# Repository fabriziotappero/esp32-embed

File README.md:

# ESP32 Embed
This repository contains a lot of C++ projects that can help you out when doing embedded programming with the Espressif ESP32, especially the new ESP32-S2.

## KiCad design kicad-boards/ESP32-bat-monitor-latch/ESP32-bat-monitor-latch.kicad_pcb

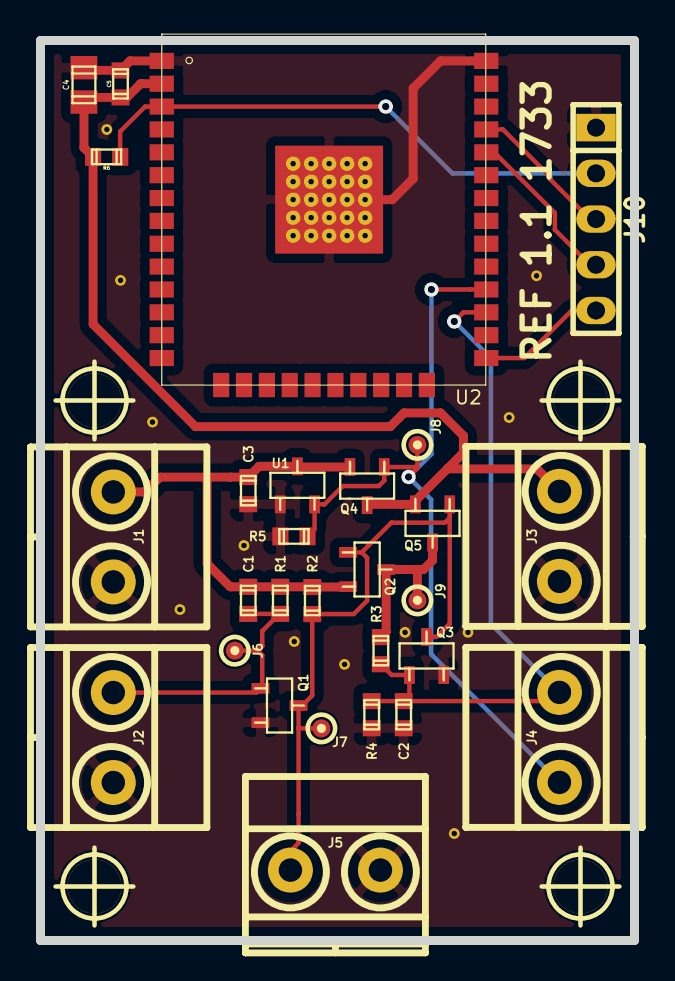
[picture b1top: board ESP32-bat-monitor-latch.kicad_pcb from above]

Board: 2 copper layers, 33.0 x 50.0 mm, 32 parts (0 on the bottom side), 12 nets.

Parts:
C1, C2, C3, C5: 100nF; c_0603
C4: 10uF; c_0805
J1, J2, J3, J4, J5: CONN_01X02; mkds_1,5-2
J6, J7, J8, J9: TEST_1P; testpoint_1mm
J10: CONN_01X05; pin_socket_5
Q1, Q3: 2N7002; sot23
Q2, Q4, Q5: AO3401; sot23
R1, R2, R4: 2M2; r_0603
R3, R5, R6: 100k; r_0603
U1: MAX809; sot23
U2: ES-WROOM-32; ESP-WROOM-32-short
hole_3mm, hole_3mm#2, hole_3mm#3, hole_3mm#4: VAL**; hole_3mm

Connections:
GND: C2.2, C3.2, C4.1, C5.1, J1.2, J2.2, J3.1, J5.2, J10.1, Q1.3, Q3.3, R4.2, R5.2, U1.1, U2.1, U2.38, U2.39
unnamed: C1.2, J2.1, J6.1, Q1.1, R1.2
unnamed: C2.1, J4.2, Q3.1, R3.2, R4.1, U2.27
unnamed: C4.2, C5.2, J3.2, Q4.2, Q5.3, R6.1, U2.2
unnamed: J4.1, J8.1, Q4.1, R5.1, U1.3, U2.28
unnamed: J5.1, J7.1, Q1.2, Q2.1, Q3.2, Q5.1, R2.2
unnamed: J9.1, Q2.2, Q5.2, R3.1
unnamed: J10.2, R6.2, U2.3
unnamed: J10.3, U2.35
unnamed: J10.4, U2.34
unnamed: J10.5, U2.25
VCC: C1.1, C3.1, J1.1, Q2.3, Q4.3, R1.1, R2.1, U1.2

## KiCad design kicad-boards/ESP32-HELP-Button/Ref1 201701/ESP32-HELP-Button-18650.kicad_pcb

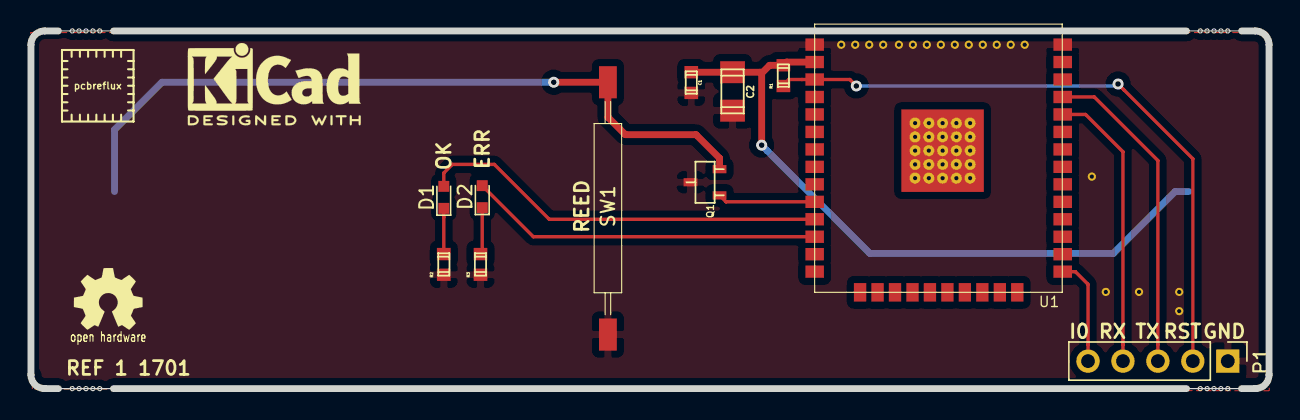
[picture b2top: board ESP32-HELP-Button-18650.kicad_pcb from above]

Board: 2 copper layers, 90.0 x 26.0 mm, 12 parts (1 on the bottom side), 12 nets.

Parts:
BT2: Battery; 18650_Battery_Holder_SMT
C1: 100nF; c_0603
C2: 10uF; c_1206
D1, D2: LED; LED_0603
P1: CONN_01X05; Pin_Header_Straight_1x05_Pitch2.54mm
Q1: Q_NMOS_GDS; sot23
R1: 10K; r_0603
R2, R3: 330R; r_0603
SW1: SW_PUSH; SMD_Reed_Switch
U1: ES-WROOM-32; ESP-WROOM-32-short

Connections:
/GND: C1.1, C2.1, P1.1, Q1.2, R2.2, R3.2, SW1.2, U1.1, U1.38
unnamed: BT2.1, C1.2, C2.2, R1.2, U1.2
unnamed: BT2.2, Q1.3, SW1.1
unnamed: D1.1, R2.1
unnamed: D1.2, U1.11
unnamed: D2.1, R3.1
unnamed: D2.2, U1.12
unnamed: P1.2, R1.1, U1.3
unnamed: P1.3, U1.35
unnamed: P1.4, U1.34
unnamed: P1.5, U1.25
unnamed: Q1.1, U1.10

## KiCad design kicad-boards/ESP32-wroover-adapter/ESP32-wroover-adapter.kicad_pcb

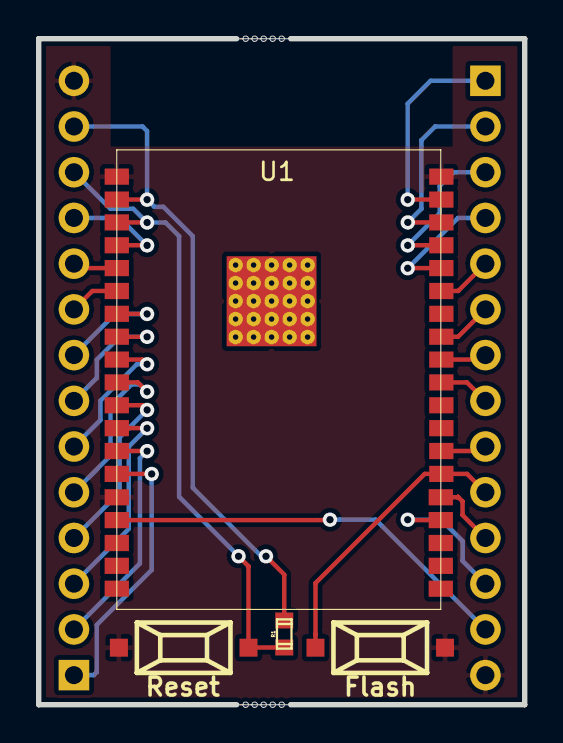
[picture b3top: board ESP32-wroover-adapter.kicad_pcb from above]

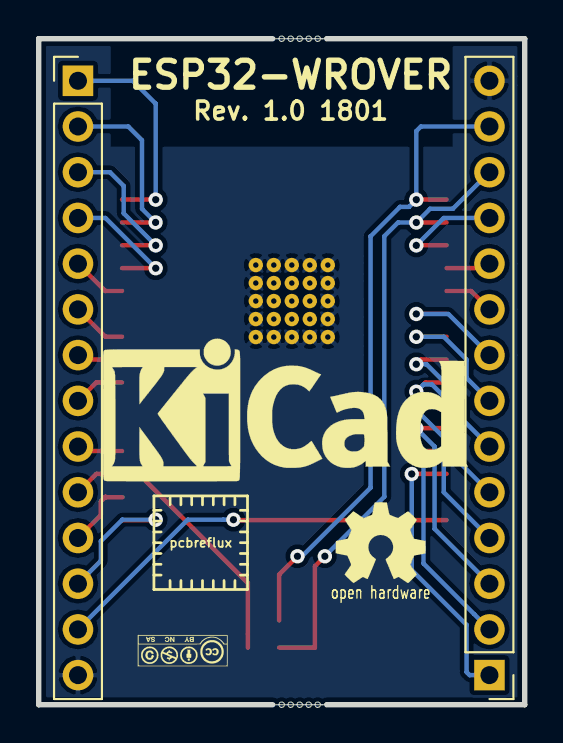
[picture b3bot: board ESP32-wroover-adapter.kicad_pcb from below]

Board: 2 copper layers, 27.0 x 37.0 mm, 6 parts (2 on the bottom side), 27 nets.

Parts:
J1, J2: CONN_01X14; Pin_Header_Straight_1x14_Pitch2.54mm
R1: 100K; r_0603
SW1, SW2: SW_PUSH; smd_push
U1: ESP32-WROVER; ESP32-WROVER-short

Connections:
+3V3: J1.13, R1.1, U1.2
GND: J1.14, J2.14, SW1.1, SW2.2, U1.1, U1.15, U1.38, U1.39
unnamed: J1.1, U1.14
unnamed: J1.2, U1.13
unnamed: J1.3, U1.12
unnamed: J1.4, U1.11
unnamed: J1.5, U1.10
unnamed: J1.6, U1.9
unnamed: J1.7, U1.8
unnamed: J1.8, U1.7
unnamed: J1.9, U1.6
unnamed: J1.10, U1.5
unnamed: J1.11, U1.4
unnamed: J1.12, R1.2, SW1.2, U1.3
unnamed: J2.1, U1.37
unnamed: J2.2, U1.36
unnamed: J2.3, U1.35
unnamed: J2.4, U1.34
unnamed: J2.5, U1.33
unnamed: J2.6, U1.31
unnamed: J2.7, U1.30
unnamed: J2.8, U1.29
unnamed: J2.9, U1.26
unnamed: J2.10, SW2.1, U1.25
unnamed: J2.11, U1.24
unnamed: J2.12, U1.23
unnamed: J2.13, U1.16

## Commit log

2020-05-14 first
2020-05-14 more things
